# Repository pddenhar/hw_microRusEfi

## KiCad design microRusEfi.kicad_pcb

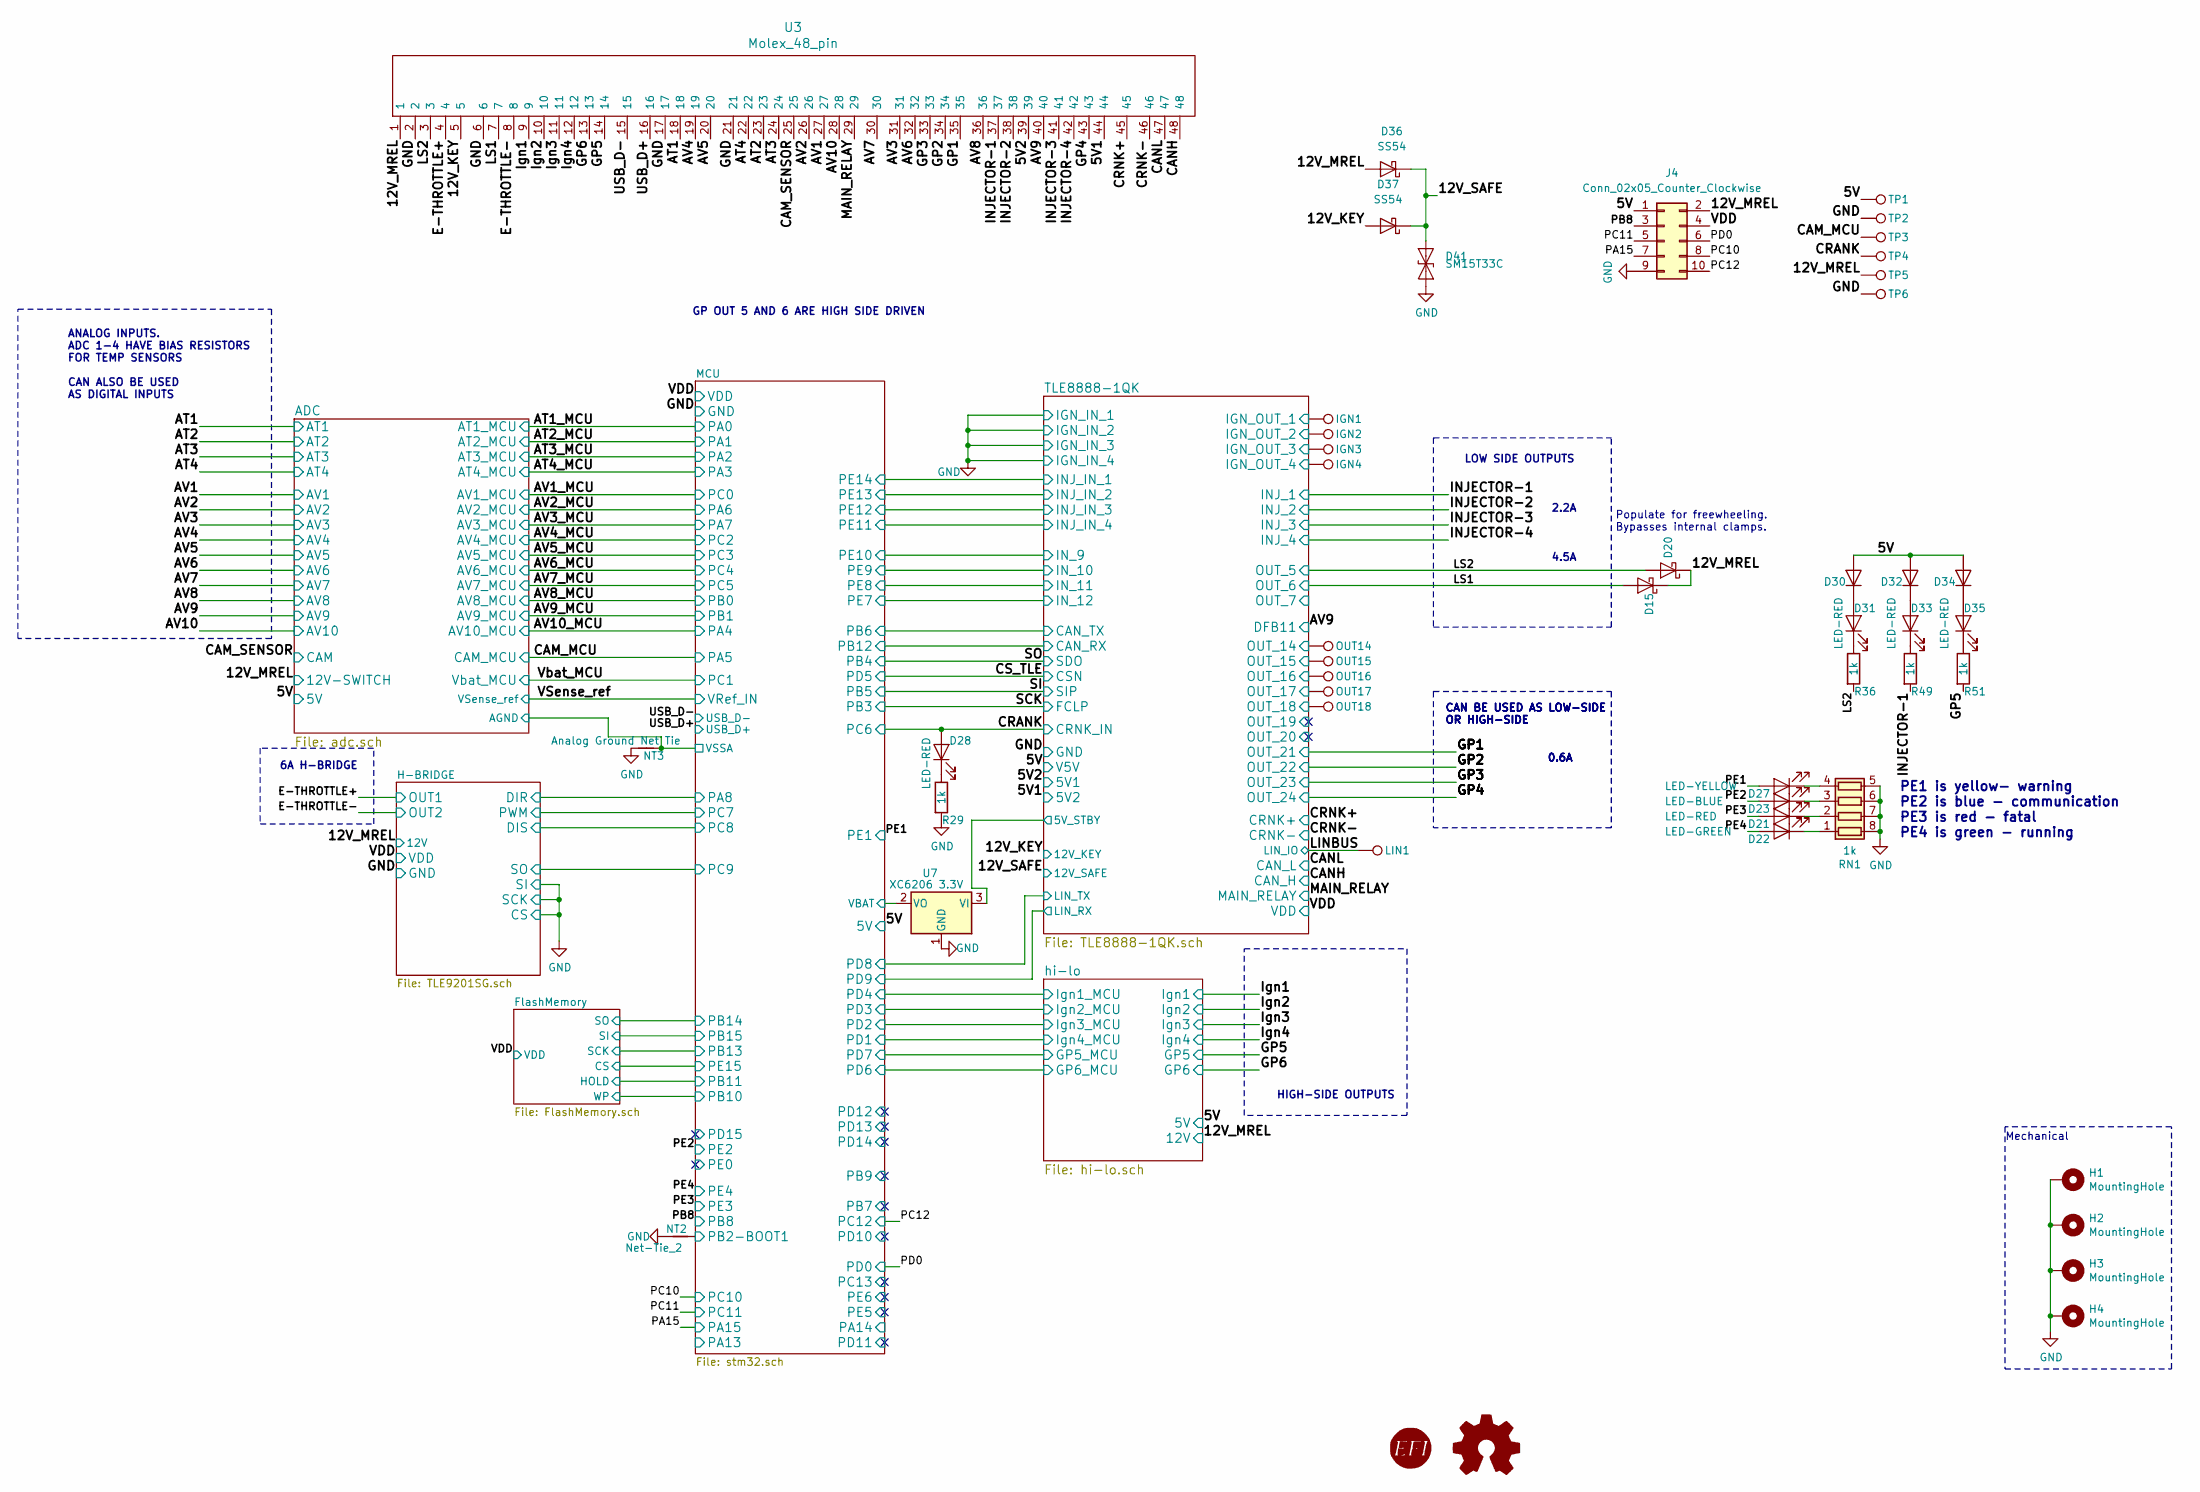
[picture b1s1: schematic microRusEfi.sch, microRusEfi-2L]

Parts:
D15, D20: DNP; D_SOD-323; Part # NSR0530HT
D21: LED-RED; LED_0805_2012Metric; LCSC C84256
D22: LED-GREEN; LED_0805_2012Metric; LCSC C2297
D23: LED-BLUE; LED_0805_2012Metric; LCSC C2293
D27: LED-YELLOW; LED_0805_2012Metric; LCSC C2296
D28: LED-RED; LED_0603_1608Metric; Part # LTST-C193TBKT-5A; LCSC C2286
D30, D32, D34: 1N4148WS; D_SOD-323; Part # NSR0530HT; LCSC C2128
D31, D33, D35: LED-RED; LED_0603_1608Metric; Part # LTST-S270KRKT; LCSC C2286
D36, D37: SS54; D_SMA; LCSC C22452
D41: SM15T33C; D_SMC
H1, H2, H3, H4: MountingHole; MountingHole_3.5mm_Pad_Via; Part # DNP
IGN1, IGN2, IGN3, IGN4: IGNOUT; Pin_D0.7mm_L6.5mm_W1.8mm_FlatFork; Part # DNP
J4: Conn_02x05_Counter_Clockwise; PinHeader_2x05_P2.54mm_Vertical_SMD
LIN1: LIN; PinHeader_1x01_P2.54mm_Vertical; Part # DNP
LOGO1: DNP; LogoMRE; Part # DNP
LOGO2: DNP; LOGO; Part # DNP
NT2: Net-Tie_2; Net-Tie_2_8.5mil
NT3: Analog Ground Net Tie; NetTie-2_SMD_Pad0.5mm
OUT14: OUT14; Pin_D0.7mm_L6.5mm_W1.8mm_FlatFork; Part # DNP
OUT15: OUT15; Pin_D0.7mm_L6.5mm_W1.8mm_FlatFork; Part # DNP
OUT16: OUT16; Pin_D0.7mm_L6.5mm_W1.8mm_FlatFork; Part # DNP
OUT17: OUT17; Pin_D0.7mm_L6.5mm_W1.8mm_FlatFork; Part # DNP
OUT18: OUT18; Pin_D0.7mm_L6.5mm_W1.8mm_FlatFork; Part # DNP
R29, R36, R49, R51: 1k; R_0603_1608Metric; Part # RMCF0603JJ1K00; LCSC C21190
RN1: 1k; R_Array_Convex_4x0603; Part # CAT16-1001F4LF; LCSC C20197
TP1, TP5: 5V; TestPoint_Pad_D2.0mm; Part # DNP
TP2, TP6: GND; TestPoint_Pad_D2.0mm; Part # DNP
TP3, TP4: TP; TestPoint_Pad_D2.0mm; Part # DNP
U3: Molex_48_pin; Molex_48; Part # 500762-0481
U7: XC6206 3.3V; SOT-23; LCSC C5446

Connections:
/5V: D30.2 (A), D32.2 (A), D34.2 (A), J4.1, TP1.1; also elsewhere on the board
/5V1: U3.44; also elsewhere on the board
/5V2: U3.39; also elsewhere on the board
/12V_KEY: D37.2 (A), U3.5; also elsewhere on the board
/12V_MREL: D15.1 (K), D20.1 (K), D36.2 (A), J4.2, TP5.1, U3.1; also elsewhere on the board
/12V_SAFE: D36.1 (K), D37.1 (K), D41.1 (A1); also elsewhere on the board
/ADC/AGND: NT3.2; also elsewhere on the board
/AT1: U3.18; also elsewhere on the board
/AT2: U3.23; also elsewhere on the board
/AT3: U3.24; also elsewhere on the board
/AT4: U3.22; also elsewhere on the board
/AV1: U3.27; also elsewhere on the board
/AV2: U3.26; also elsewhere on the board
/AV3: U3.31; also elsewhere on the board
/AV4: U3.19; also elsewhere on the board
/AV5: U3.20; also elsewhere on the board
/AV6: U3.32; also elsewhere on the board
/AV7: U3.30; also elsewhere on the board
/AV8: U3.36; also elsewhere on the board
/AV9: U3.40; also elsewhere on the board
/AV10: U3.28; also elsewhere on the board
/CAM_MCU: TP3.1; also elsewhere on the board
/CAM_SENSOR: U3.25; also elsewhere on the board
/CANH: U3.48; also elsewhere on the board
/CANL: U3.47; also elsewhere on the board
/CRANK: D28.2 (A), TP4.1; also elsewhere on the board
/CRNK+: U3.45; also elsewhere on the board
/CRNK-: U3.46; also elsewhere on the board
/E-THROTTLE+: U3.4; also elsewhere on the board
/E-THROTTLE-: U3.8; also elsewhere on the board
/GP1: U3.35; also elsewhere on the board
/GP2: U3.34; also elsewhere on the board
/GP3: U3.33; also elsewhere on the board
/GP4: U3.43; also elsewhere on the board
/GP5: R51.2, U3.14; also elsewhere on the board
/GP6: U3.13; also elsewhere on the board
/INJECTOR-1: R49.2, U3.37; also elsewhere on the board
/INJECTOR-2: U3.38; also elsewhere on the board
/INJECTOR-3: U3.41; also elsewhere on the board
/INJECTOR-4: U3.42; also elsewhere on the board
/Ign1: U3.9; also elsewhere on the board
/Ign2: U3.10; also elsewhere on the board
/Ign3: U3.11; also elsewhere on the board
/Ign4: U3.12; also elsewhere on the board
/LINBUS: LIN1.1; also elsewhere on the board
/LS1: D15.2 (A), U3.7; also elsewhere on the board
/LS2: D20.2 (A), R36.2, U3.3; also elsewhere on the board
/MAIN_RELAY: U3.29; also elsewhere on the board
/MCU/PB2-BOOT1: NT2.2; also elsewhere on the board
/MCU/VBAT: U7.2 (VO); also elsewhere on the board
/PA15: J4.7; also elsewhere on the board
/PB8: J4.3; also elsewhere on the board
/PC10: J4.8; also elsewhere on the board
/PC11: J4.5; also elsewhere on the board
/PC12: J4.10; also elsewhere on the board
/PD0: J4.6; also elsewhere on the board
/PE1: D27.2 (A); also elsewhere on the board
/PE2: D23.2 (A); also elsewhere on the board
/PE3: D21.2 (A); also elsewhere on the board
/PE4: D22.2 (A); also elsewhere on the board
/TLE8888-1QK/5V_STBY: U7.3 (VI); also elsewhere on the board
/TLE8888-1QK/IGN_OUT_1: IGN1.1; also elsewhere on the board
/TLE8888-1QK/IGN_OUT_2: IGN2.1; also elsewhere on the board
/TLE8888-1QK/IGN_OUT_3: IGN3.1; also elsewhere on the board
/TLE8888-1QK/IGN_OUT_4: IGN4.1; also elsewhere on the board
/TLE8888-1QK/OUT_14: OUT14.1; also elsewhere on the board
/TLE8888-1QK/OUT_15: OUT15.1; also elsewhere on the board
/TLE8888-1QK/OUT_16: OUT16.1; also elsewhere on the board
/TLE8888-1QK/OUT_17: OUT17.1; also elsewhere on the board
/TLE8888-1QK/OUT_18: OUT18.1; also elsewhere on the board
/USB_D+: U3.16; also elsewhere on the board
/USB_D-: U3.15; also elsewhere on the board
/VDD: J4.4; also elsewhere on the board
GND: D41.2 (A2), H1.1, H2.1, H3.1, H4.1, J4.9, NT2.1, NT3.1, R29.2, RN1.5 (R4.2), RN1.6 (R3.2), RN1.7 (R2.2), RN1.8 (R1.2), TP2.1, TP6.1, U3.2, U3.6, U3.17, U3.21, U7.1 (GND); also elsewhere on the board
unnamed: D21.1 (K), RN1.2 (R2.1)
unnamed: D22.1 (K), RN1.1 (R1.1)
unnamed: D23.1 (K), RN1.3 (R3.1)
unnamed: D27.1 (K), RN1.4 (R4.1)
unnamed: D28.1 (K), R29.1
unnamed: D30.1 (K), D31.2 (A)
unnamed: D31.1 (K), R36.1
unnamed: D32.1 (K), D33.2 (A)
unnamed: D33.1 (K), R49.1
unnamed: D34.1 (K), D35.2 (A)
unnamed: D35.1 (K), R51.1

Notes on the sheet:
LOW SIDE OUTPUTS
4.5A
0.6A
2.2A
HIGH-SIDE OUTPUTS
ANALOG INPUTS. ADC 1-4 HAVE BIAS RESISTORS FOR TEMP SENSORS CAN ALSO BE USED AS DIGITAL INPUTS
CAN BE USED AS LOW-SIDE OR HIGH-SIDE
GP OUT 5 AND 6 ARE HIGH SIDE DRIVEN
6A H-BRIDGE
PE1 is yellow- warning PE2 is blue - communication PE3 is red - fatal PE4 is green - running
Populate for freewheeling. Bypasses internal clamps.
Mechanical

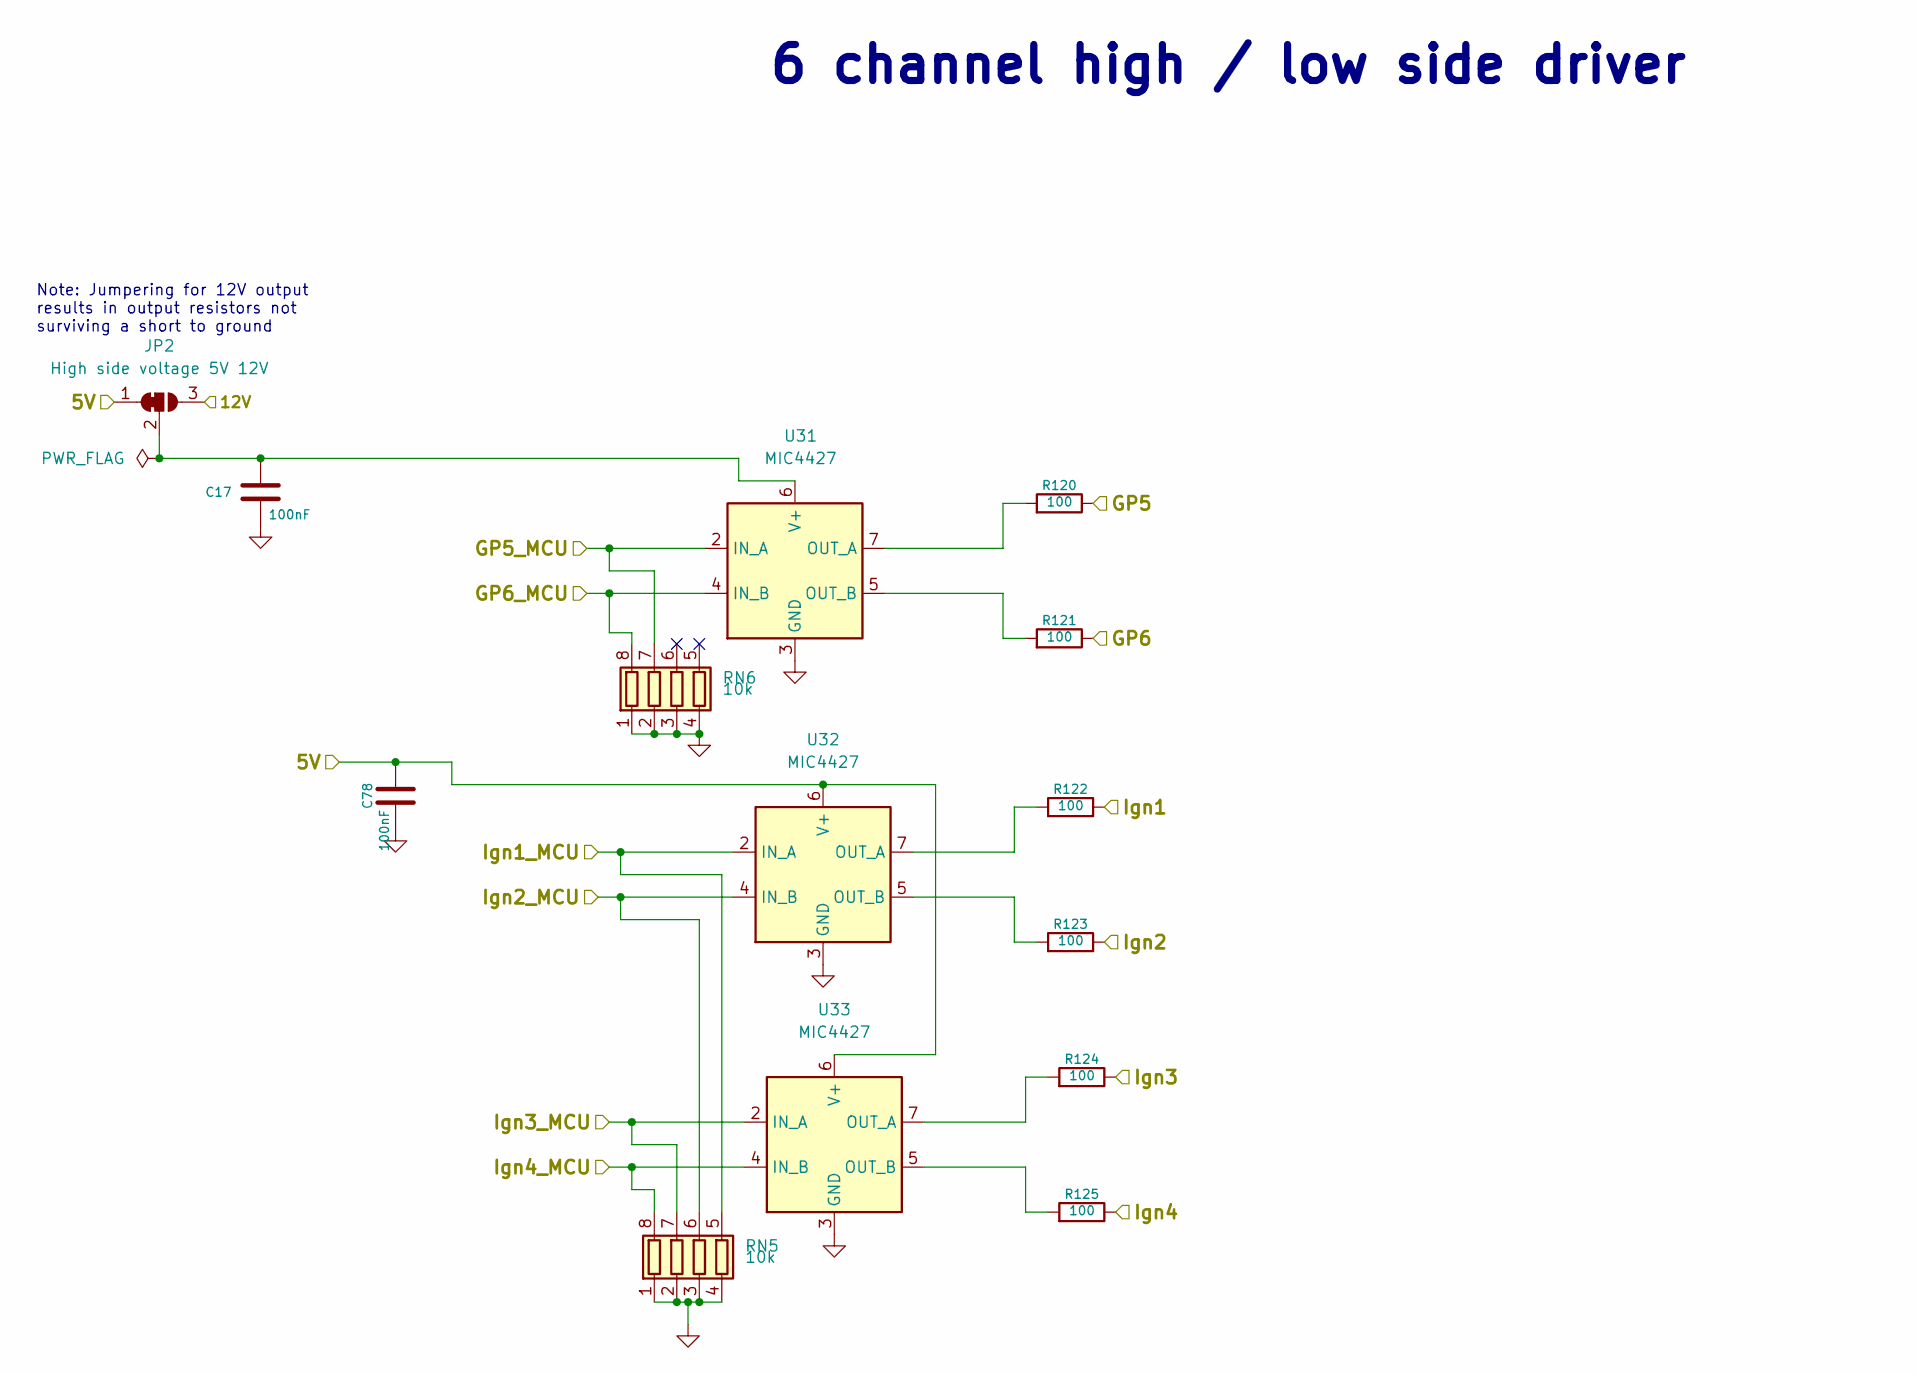
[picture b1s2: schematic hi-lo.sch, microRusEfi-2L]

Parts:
C17, C78: 100nF; C_0603_1608Metric; LCSC C14663
JP2: High side voltage 5V 12V; SolderJumper-3_P1.3mm_Bridged2Bar12_Pad1.0x1.5mm
R120, R121, R122, R123, R124, R125: 100; R_1206_3216Metric; Part # RMCF0603FT100R; LCSC C17901
RN5, RN6: 10k; R_Array_Convex_4x0603; LCSC C29718
U31, U32, U33: MIC4427; SOIC-8_3.9x4.9mm_P1.27mm; LCSC C144205

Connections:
/5V: C78.1, JP2.1 (A), U32.6 (V+), U33.6 (V+); also elsewhere on the board
/12V_MREL: JP2.3 (B); also elsewhere on the board
/GP5: R120.1; also elsewhere on the board
/GP6: R121.1; also elsewhere on the board
/Ign1: R122.1; also elsewhere on the board
/Ign2: R123.1; also elsewhere on the board
/Ign3: R124.1; also elsewhere on the board
/Ign4: R125.1; also elsewhere on the board
/hi-lo/GP5_MCU: RN6.7 (R2.2), U31.2 (IN_A); also elsewhere on the board
/hi-lo/GP6_MCU: RN6.8 (R1.2), U31.4 (IN_B); also elsewhere on the board
/hi-lo/Ign1_MCU: RN5.5 (R4.2), U32.2 (IN_A); also elsewhere on the board
/hi-lo/Ign2_MCU: RN5.6 (R3.2), U32.4 (IN_B); also elsewhere on the board
/hi-lo/Ign3_MCU: RN5.7 (R2.2), U33.2 (IN_A); also elsewhere on the board
/hi-lo/Ign4_MCU: RN5.8 (R1.2), U33.4 (IN_B); also elsewhere on the board
GND: C17.2, C78.2, RN5.1 (R1.1), RN5.2 (R2.1), RN5.3 (R3.1), RN5.4 (R4.1), RN6.1 (R1.1), RN6.2 (R2.1), RN6.3 (R3.1), RN6.4 (R4.1), U31.3 (GND), U32.3 (GND), U33.3 (GND); also elsewhere on the board
unnamed: C17.1, JP2.2 (C), U31.6 (V+)
unnamed: R120.2, U31.7 (OUT_A)
unnamed: R121.2, U31.5 (OUT_B)
unnamed: R122.2, U32.7 (OUT_A)
unnamed: R123.2, U32.5 (OUT_B)
unnamed: R124.2, U33.7 (OUT_A)
unnamed: R125.2, U33.5 (OUT_B)

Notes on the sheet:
6 channel high / low side driver
Note: Jumpering for 12V output results in output resistors not surviving a short to ground

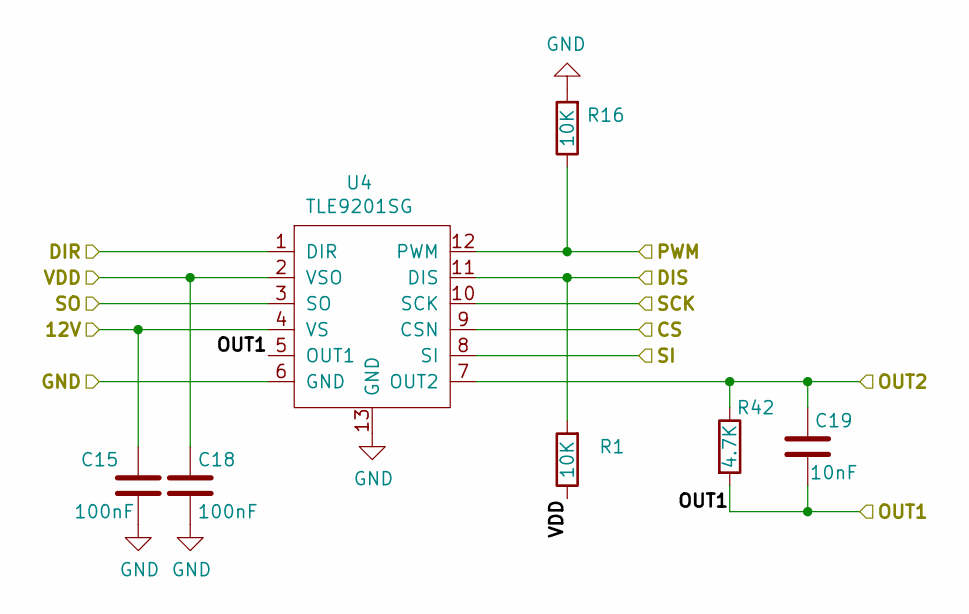
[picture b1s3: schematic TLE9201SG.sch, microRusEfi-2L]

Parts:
C15, C18: 100nF; C_0603_1608Metric; Part # C0603C104J5RACTU; LCSC C14663
C19: 10nF; C_0603_1608Metric; Part # C0603C103K1RACTU; LCSC C57112
R1, R16: 10K; R_0603_1608Metric; Part # RMCF0603JT10K0; LCSC C25804
R42: 4.7K; R_0603_1608Metric; Part # RMCF0603JT4K70; LCSC C23162
U4: TLE9201SG; Infineon_PG-DSO-12-11; Part # TLE9201SG

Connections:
/12V_MREL: C15.1, U4.4 (VS); also elsewhere on the board
/E-THROTTLE+: C19.2, R42.2, U4.5 (OUT1); also elsewhere on the board
/E-THROTTLE-: C19.1, R42.1, U4.7 (OUT2); also elsewhere on the board
/H-BRIDGE/DIR: U4.1 (DIR); also elsewhere on the board
/H-BRIDGE/DIS: R1.2, U4.11 (DIS); also elsewhere on the board
/MCU/PC7: R16.1, U4.12 (PWM); also elsewhere on the board
/MCU/PC9: U4.3 (SO); also elsewhere on the board
/VDD: C18.1, R1.1, U4.2 (VSO); also elsewhere on the board
GND: C15.2, C18.2, R16.2, U4.6 (GND), U4.8 (SI), U4.9 (CSN), U4.10 (SCK), U4.13 (GND); also elsewhere on the board

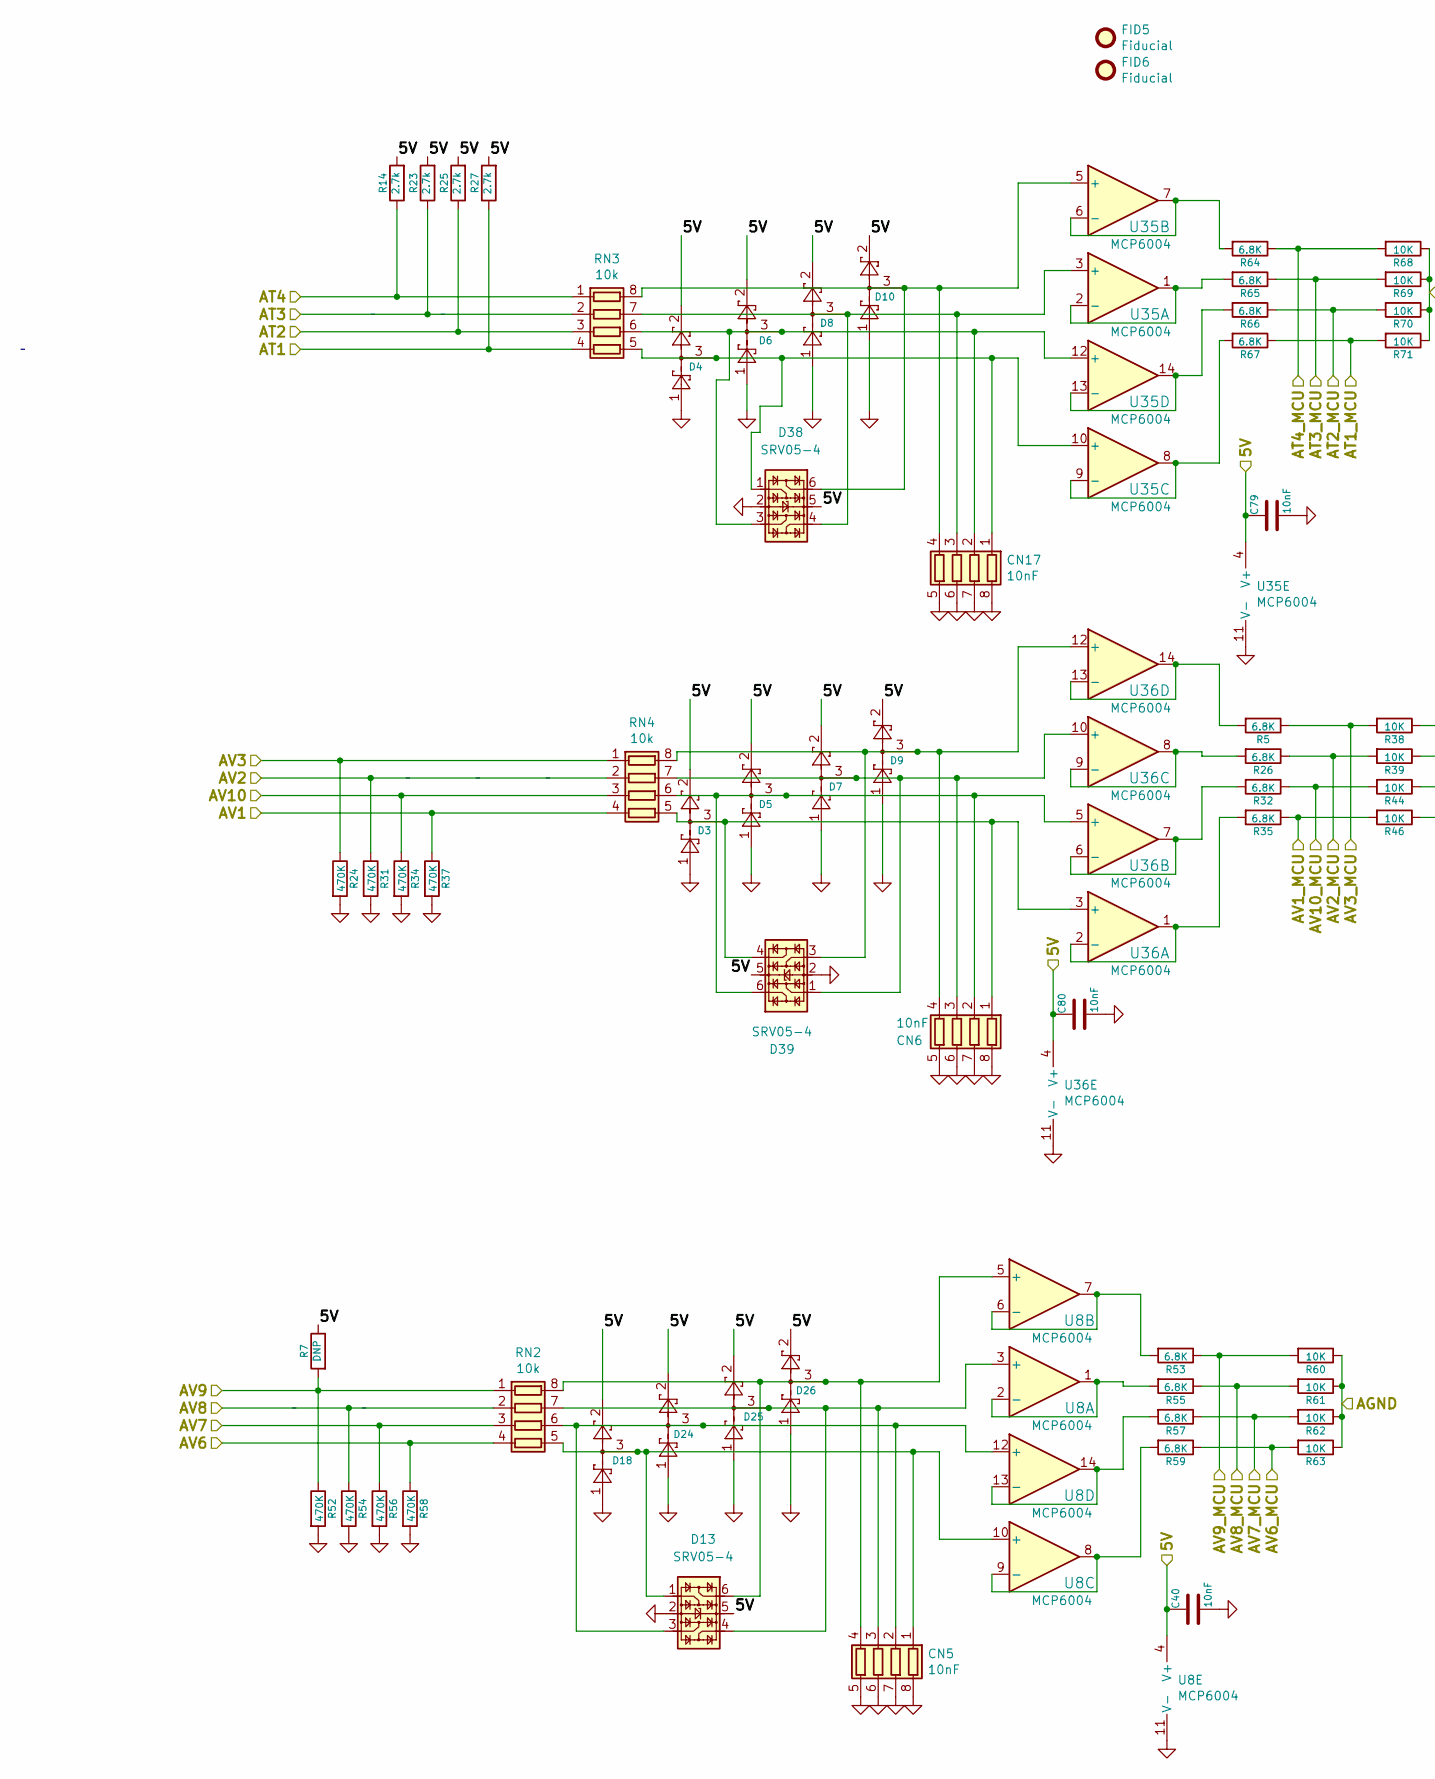
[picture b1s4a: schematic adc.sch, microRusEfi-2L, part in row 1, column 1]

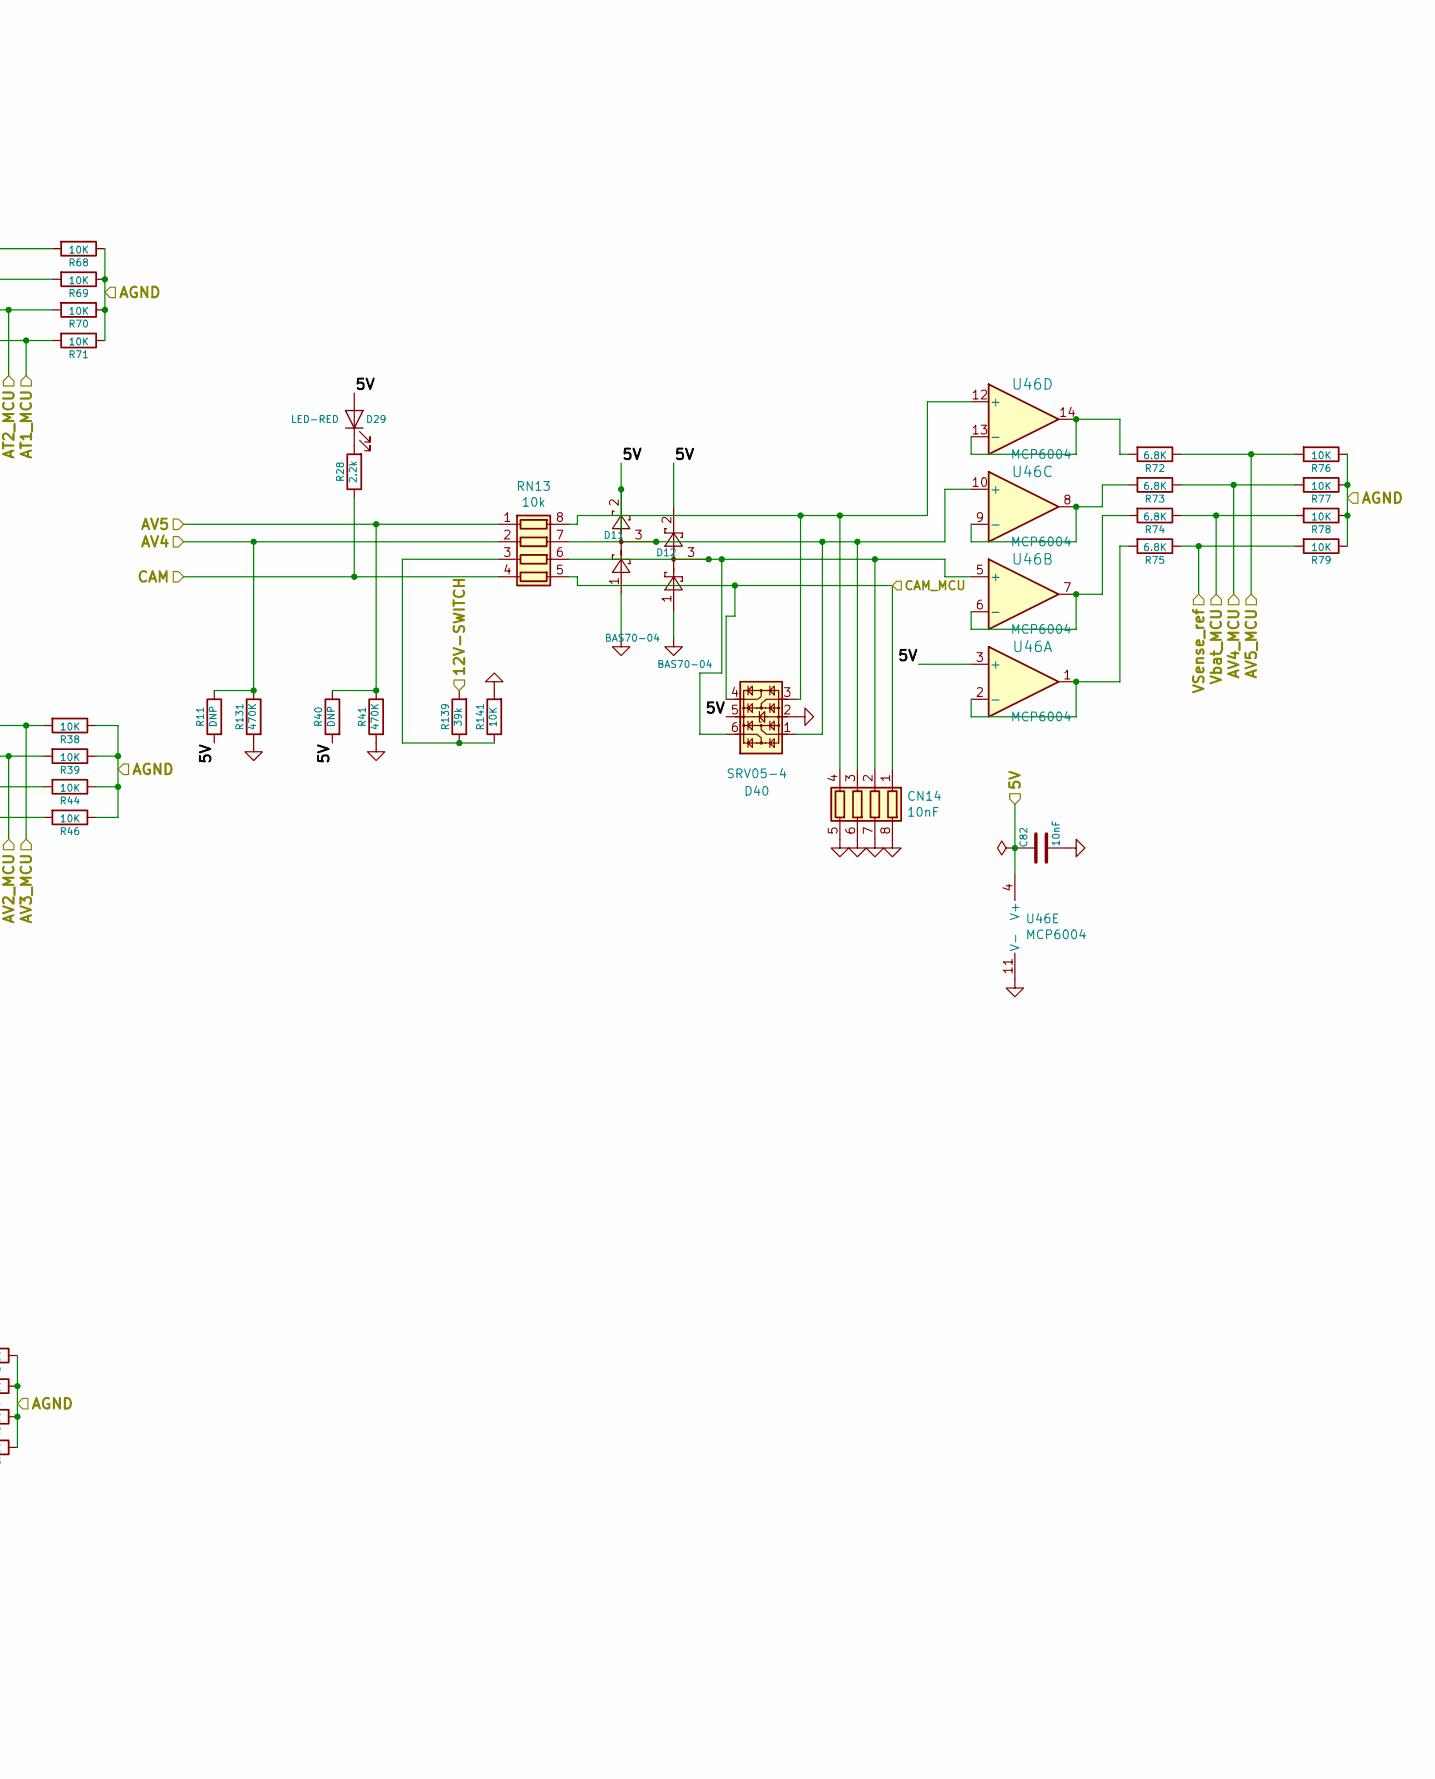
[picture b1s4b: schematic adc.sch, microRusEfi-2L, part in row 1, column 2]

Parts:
C40, C79, C80, C82: 10nF; C_0603_1608Metric; Part # C0603C103K1RACTU; LCSC C57112
CN5, CN6, CN14, CN17: 10nF; R_Array_Convex_4x0603; Part # CA064X103K2RACAUTO
D3, D4, D5, D6, D7, D8, D9, D10, D11, D12, D18, D24, D25, D26: BAS70-04; SOT-23; Part # SBAS70-04LT1G
D13, D38, D39, D40: SRV05-4; SOT-23-6; LCSC C85364
D29: LED-RED; LED_0603_1608Metric; Part # LTST-C193TBKT-5A; LCSC C2286
FID5, FID6: Fiducial; Fiducial_0.5mm_Mask1mm; Part # DNP
R5, R26, R32, R35, R53, R55, R57, R59, R64, R65, R66, R67, R72, R73, R74, R75: 6.8K; R_0603_1608Metric; LCSC C23212
R7, R11, R40: DNP; R_0603_1608Metric; Part # DNP
R14, R23, R25, R27: 2.7k; R_0603_1608Metric; Part # RMCF0603FT2K70; LCSC C13167
R24, R31, R34, R37, R41, R52, R54, R56, R58, R131: 470K; R_0603_1608Metric; Part # RMCF0603FT470K; LCSC C23178
R28: 2.2k; R_0603_1608Metric; Part # RMCF0603FT2K20; LCSC C4190
R38, R39, R44, R46, R60, R61, R62, R63, R68, R69, R70, R71, R76, R77, R78, R79: 10K; R_0603_1608Metric; LCSC C25804
R139: 39k; R_0603_1608Metric; Part # RC0603FR-0739KL; LCSC C23153
R141: 10K; R_0603_1608Metric; Part # RMCF0603JT10K0; LCSC C25804
RN2, RN3, RN4, RN13: 10k; R_Array_Convex_4x0603; Part # YC164-JR-0710KL; LCSC C29718
U8, U35, U36, U46: MCP6004; TSSOP-14_4.4x5mm_P0.65mm; Part # MCP6004T-I/ST; LCSC C50282

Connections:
/5V: C40.1, C79.1, C80.1, C82.1, D3.2, D4.2, D5.2, D6.2, D7.2, D8.2, D9.2, D10.2, D11.2, D12.2, D13.5, D18.2, D24.2, D25.2, D26.2, D29.2 (A), D38.5, D39.5, D40.5, R7.1, R11.2, R14.2, R23.2, R25.2, R27.2, R40.2, U8.4 (V+), U35.4 (V+), U36.4 (V+), U46.3 (+), U46.4 (V+); also elsewhere on the board
/12V_MREL: R139.2; also elsewhere on the board
/ADC/AGND: R38.1, R39.1, R44.1, R46.1, R60.1, R61.1, R62.1, R63.1, R68.1, R69.1, R70.1, R71.1, R76.1, R77.1, R78.1, R79.1; also elsewhere on the board
/AT1: R27.1, RN3.4 (R4.1); also elsewhere on the board
/AT1_MCU: R67.1, R71.2; also elsewhere on the board
/AT2: R25.1, RN3.3 (R3.1); also elsewhere on the board
/AT2_MCU: R66.1, R70.2; also elsewhere on the board
/AT3: R23.1, RN3.2 (R2.1); also elsewhere on the board
/AT3_MCU: R65.1, R69.2; also elsewhere on the board
/AT4: R14.1, RN3.1 (R1.1); also elsewhere on the board
/AT4_MCU: R64.1, R68.2; also elsewhere on the board
/AV1: R37.1, RN4.4 (R4.1); also elsewhere on the board
/AV1_MCU: R35.1, R46.2; also elsewhere on the board
/AV2: R31.1, RN4.2 (R2.1); also elsewhere on the board
/AV2_MCU: R26.1, R39.2; also elsewhere on the board
/AV3: R24.1, RN4.1 (R1.1); also elsewhere on the board
/AV3_MCU: R5.1, R38.2; also elsewhere on the board
/AV4: R11.1, R131.1, RN13.2 (R2.1); also elsewhere on the board
/AV4_MCU: R73.1, R77.2; also elsewhere on the board
/AV5: R40.1, R41.1, RN13.1 (R1.1); also elsewhere on the board
/AV5_MCU: R72.1, R76.2; also elsewhere on the board
/AV6: R58.1, RN2.4 (R4.1); also elsewhere on the board
/AV6_MCU: R59.1, R63.2; also elsewhere on the board
/AV7: R56.1, RN2.3 (R3.1); also elsewhere on the board
/AV7_MCU: R57.1, R62.2; also elsewhere on the board
/AV8: R54.1, RN2.2 (R2.1); also elsewhere on the board
/AV8_MCU: R55.1, R61.2; also elsewhere on the board
/AV9: R7.2, R52.1, RN2.1 (R1.1); also elsewhere on the board
/AV9_MCU: R53.1, R60.2; also elsewhere on the board
/AV10: R34.1, RN4.3 (R3.1); also elsewhere on the board
/AV10_MCU: R32.1, R44.2; also elsewhere on the board
/CAM_MCU: CN14.1 (R1.1), D40.4, RN13.5 (R4.2); also elsewhere on the board
/CAM_SENSOR: R28.1, RN13.4 (R4.1); also elsewhere on the board
/VSense_ref: R75.1, R79.2; also elsewhere on the board
/Vbat_MCU: R74.1, R78.2; also elsewhere on the board
GND: C40.2, C79.2, C80.2, C82.2, CN5.5 (R4.2), CN5.6 (R3.2), CN5.7 (R2.2), CN5.8 (R1.2), CN6.5 (R4.2), CN6.6 (R3.2), CN6.7 (R2.2), CN6.8 (R1.2), CN14.5 (R4.2), CN14.6 (R3.2), CN14.7 (R2.2), CN14.8 (R1.2), CN17.5 (R4.2), CN17.6 (R3.2), CN17.7 (R2.2), CN17.8 (R1.2), D3.1, D4.1, D5.1, D6.1, D7.1, D8.1, D9.1, D10.1, D11.1, D12.1, D13.2, D18.1, D24.1, D25.1, D26.1, D38.2, D39.2, D40.2, R24.2, R31.2, R34.2, R37.2, R41.2, R52.2, R54.2, R56.2, R58.2, R131.2, R141.2, U8.11 (V-), U35.11 (V-), U36.11 (V-), U46.11 (V-); also elsewhere on the board
unnamed: CN5.1 (R1.1), D13.1, D18.3, RN2.5 (R4.2), U8.10 (+)
unnamed: CN5.2 (R2.1), D13.3, D24.3, RN2.6 (R3.2), U8.12 (+)
unnamed: CN5.3 (R3.1), D13.4, D25.3, RN2.7 (R2.2), U8.3 (+)
unnamed: CN5.4 (R4.1), D13.6, D26.3, RN2.8 (R1.2), U8.5 (+)
unnamed: CN6.1 (R1.1), D3.3, D39.4, RN4.5 (R4.2), U36.3 (+)
unnamed: CN6.2 (R2.1), D5.3, D39.6, RN4.6 (R3.2), U36.5 (+)
unnamed: CN6.3 (R3.1), D7.3, D39.1, RN4.7 (R2.2), U36.10 (+)
unnamed: CN6.4 (R4.1), D9.3, D39.3, RN4.8 (R1.2), U36.12 (+)
unnamed: CN14.2 (R2.1), D12.3, D40.6, RN13.6 (R3.2), U46.5 (+)
unnamed: CN14.3 (R3.1), D11.3, D40.1, RN13.7 (R2.2), U46.10 (+)
unnamed: CN14.4 (R4.1), D40.3, RN13.8 (R1.2), U46.12 (+)
unnamed: CN17.1 (R1.1), D4.3, D38.1, RN3.5 (R4.2), U35.10 (+)
unnamed: CN17.2 (R2.1), D6.3, D38.3, RN3.6 (R3.2), U35.12 (+)
unnamed: CN17.3 (R3.1), D8.3, D38.4, RN3.7 (R2.2), U35.3 (+)
unnamed: CN17.4 (R4.1), D10.3, D38.6, RN3.8 (R1.2), U35.5 (+)
unnamed: D29.1 (K), R28.2
unnamed: R5.2, U36.13 (-), U36.14
unnamed: R26.2, U36.8, U36.9 (-)
unnamed: R32.2, U36.6 (-), U36.7
unnamed: R35.2, U36.1, U36.2 (-)
unnamed: R53.2, U8.6 (-), U8.7
unnamed: R55.2, U8.1, U8.2 (-)
unnamed: R57.2, U8.13 (-), U8.14
unnamed: R59.2, U8.8, U8.9 (-)
unnamed: R64.2, U35.6 (-), U35.7
unnamed: R65.2, U35.1, U35.2 (-)
unnamed: R66.2, U35.13 (-), U35.14
unnamed: R67.2, U35.8, U35.9 (-)
unnamed: R72.2, U46.13 (-), U46.14
unnamed: R73.2, U46.8, U46.9 (-)
unnamed: R74.2, U46.6 (-), U46.7
unnamed: R75.2, U46.1, U46.2 (-)
unnamed: R139.1, R141.1, RN13.3 (R3.1)
